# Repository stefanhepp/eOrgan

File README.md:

README
------

This project contains various parts of a midi-organ. The project consists of four
main parts:

- The Pedalboard: a 29 note midi foot pedal, mostly ARGO compliant. This odd number of notes
  was choosen because of size restrictions (I wanted it to fit under my e-piano).
- The organ console: contains stops, a lcd display, and all connectors and hardware to wire it to a PC.
  Up to three midi keyboards can be used as input devices, as well as the midi pedalboard.
- The organ desk: a framework for all the parts, contains speakers and some additional foot-stops.
  This is also designed to hold the PC. 
- The software: A controller software which allows access to some special features of the hardware
  and sets up the software synthesizer.

License
-------
Shield: [![CC BY-SA 4.0][cc-by-sa-shield]][cc-by-sa]

This work is licensed under a
[Creative Commons Attribution-ShareAlike 4.0 International License][cc-by-sa].

[![CC BY-SA 4.0][cc-by-sa-image]][cc-by-sa]

[cc-by-sa]: http://creativecommons.org/licenses/by-sa/4.0/
[cc-by-sa-image]: https://licensebuttons.net/l/by-sa/4.0/88x31.png
[cc-by-sa-shield]: https://img.shields.io/badge/License-CC%20BY--SA%204.0-lightgrey.svg

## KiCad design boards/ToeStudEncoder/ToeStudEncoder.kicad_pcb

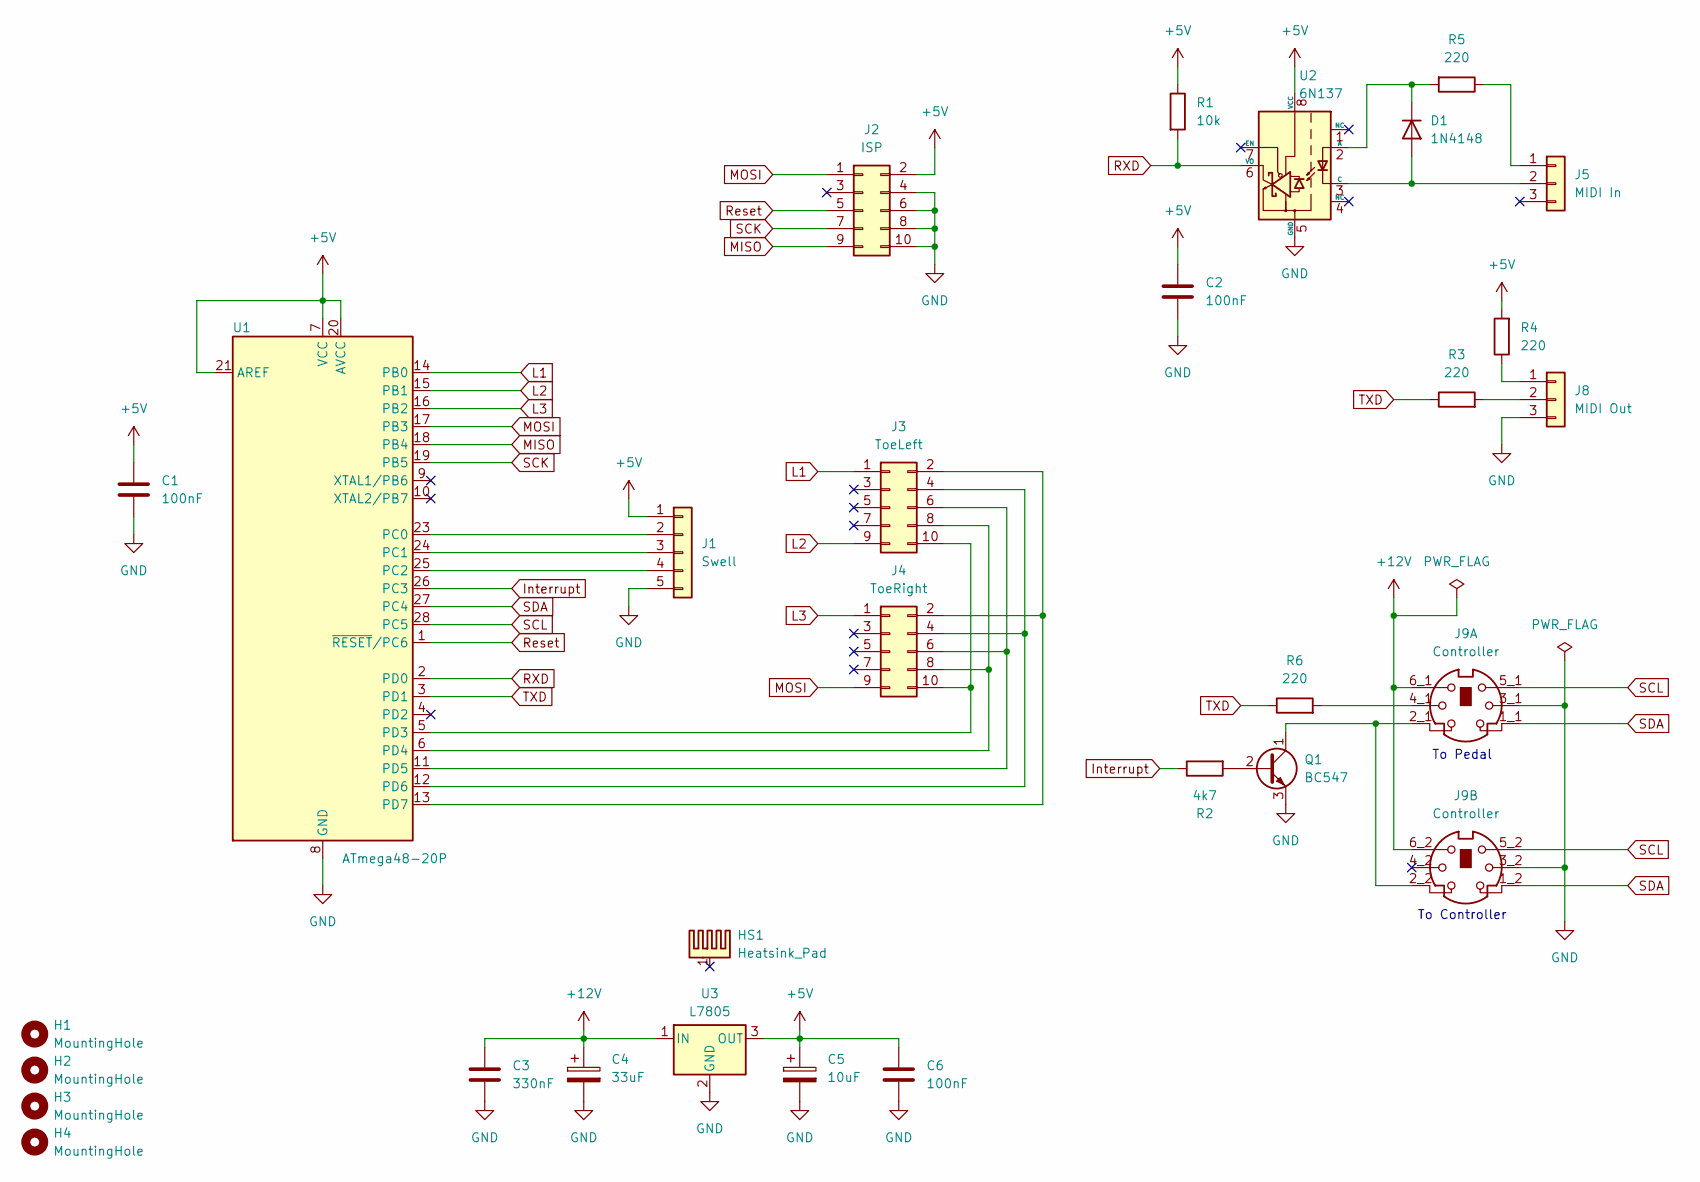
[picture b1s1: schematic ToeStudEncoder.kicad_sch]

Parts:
C1, C2: 100nF; C_Disc_D7.5mm_W2.5mm_P5.00mm
C3: 330nF; C_Disc_D4.3mm_W1.9mm_P5.00mm
C4: 33uF; CP_Radial_D7.5mm_P2.50mm
C5: 10uF; CP_Radial_D6.3mm_P2.50mm
C6: 100nF; C_Disc_D4.3mm_W1.9mm_P5.00mm
D1: 1N4148; D_DO-35_SOD27_P7.62mm_Horizontal
H1, H2, H3, H4: MountingHole; MountingHole_3mm
HS1: Heatsink_Pad; Heatsink_Aavid_TO-220_H12.7mm
J1: Swell; JST_XH_B5B-XH-A_1x05_P2.50mm_Vertical
J2: ISP; IDC-Header_2x05_P2.54mm_Vertical
J3: ToeLeft; IDC-Header_2x05_P2.54mm_Vertical
J4: ToeRight; IDC-Header_2x05_P2.54mm_Vertical
J5: MIDI In; PinHeader_1x03_P2.54mm_Vertical
J8: MIDI Out; PinHeader_1x03_P2.54mm_Vertical
J9: Controller; SWITCHCRAFT_DMD6FRA111
Q1: BC547; TO-92_Inline_Wide
R1: 10k; R_Axial_DIN0207_L6.3mm_D2.5mm_P2.54mm_Vertical
R2: 4k7; R_Axial_DIN0207_L6.3mm_D2.5mm_P2.54mm_Vertical
R3, R4, R6: 220; R_Axial_DIN0207_L6.3mm_D2.5mm_P10.16mm_Horizontal
R5: 220; R_Axial_DIN0207_L6.3mm_D2.5mm_P2.54mm_Vertical
U1: ATmega48-20P; DIP-28_W7.62mm
U2: 6N137; DIP-8_W7.62mm
U3: L7805; TO-220-3_Vertical

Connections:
+5V: C1.1, C2.1, C5.1, C6.1, J1.1, J2.2, R1.1, R4.2, U1.7 (VCC), U1.20 (AVCC), U1.21 (AREF), U2.8 (VCC), U3.3 (OUT)
+12V: C3.1, C4.1, J9.6_1, J9.6_2, U3.1 (IN)
GND: C1.2, C2.2, C3.2, C4.2, C5.2, C6.2, J1.5, J2.4, J2.6, J2.8, J2.10, J8.3, J9.3_1, J9.3_2, Q1.3 (E), U1.8 (GND), U1.22 (GND), U2.5 (GND), U3.2 (GND)
Interrupt: R2.1, U1.26 (PC3)
L1: J3.1, U1.14 (PB0)
L2: J3.9, U1.15 (PB1)
L3: J4.1, U1.16 (PB2)
MISO: J2.9, U1.18 (PB4)
MOSI: J2.1, J4.9, U1.17 (PB3)
unnamed: D1.2 (A), J5.2, U2.3 (C)
unnamed: D1.1 (K), R5.2, U2.2 (A)
unnamed: J1.2, U1.23 (PC0)
unnamed: J1.3, U1.24 (PC1)
unnamed: J1.4, U1.25 (PC2)
unnamed: J3.2, J4.2, U1.13 (PD7)
unnamed: J3.4, J4.4, U1.12 (PD6)
unnamed: J3.6, J4.6, U1.11 (PD5)
unnamed: J3.8, J4.8, U1.6 (PD4)
unnamed: J3.10, J4.10, U1.5 (PD3)
unnamed: J5.1, R5.1
unnamed: J8.1, R4.1
unnamed: J8.2, R3.2
unnamed: J9.4_1, R6.2
unnamed: Q1.2 (B), R2.2
unnamed: J9.2_1, J9.2_2, Q1.1 (C)
RXD: R1.2, U1.2 (PD0), U2.6 (VO)
Reset: J2.5, U1.1 (~RESET/PC6)
SCK: J2.7, U1.19 (PB5)
SCL: J9.5_1, J9.5_2, U1.28 (PC5)
SDA: J9.1_1, J9.1_2, U1.27 (PC4)
TXD: R3.1, R6.1, U1.3 (PD1)

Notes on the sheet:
To Controller
To Pedal

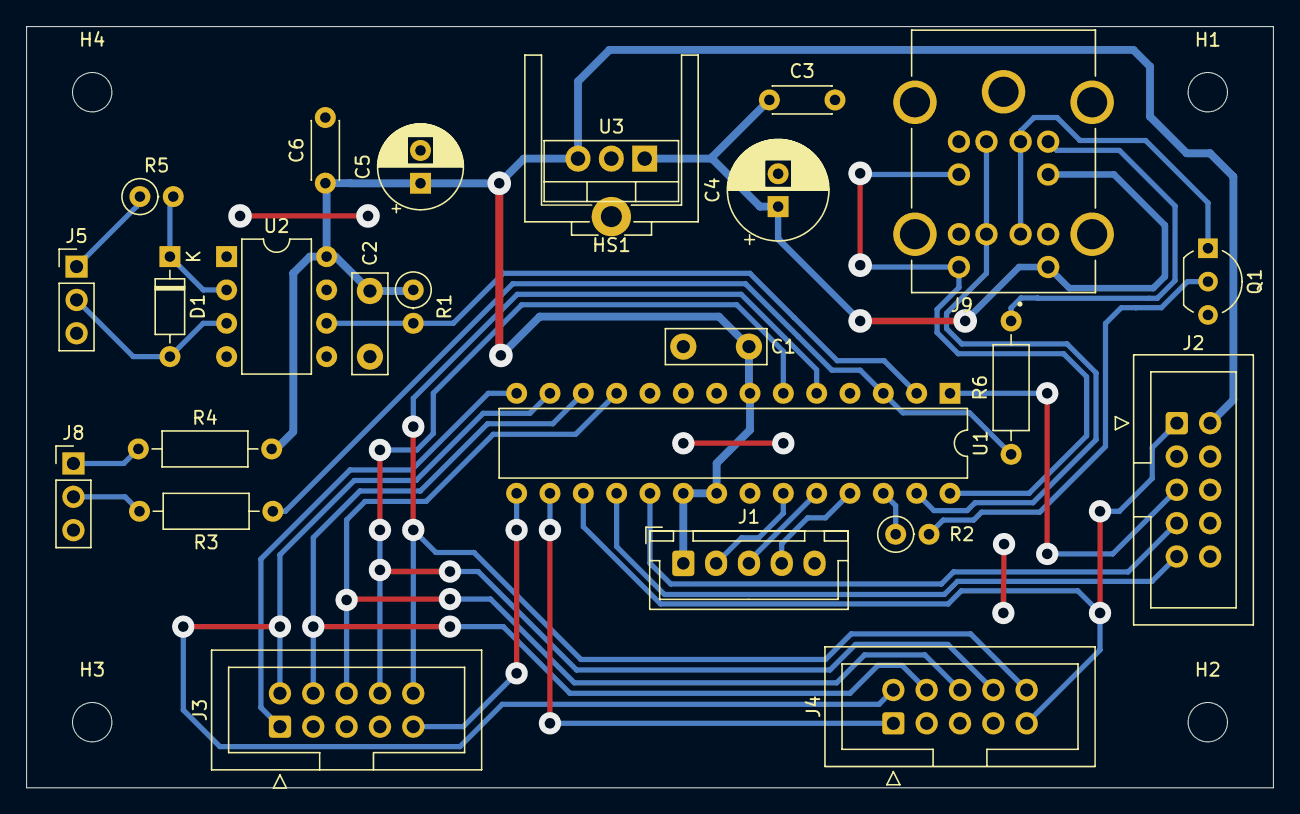
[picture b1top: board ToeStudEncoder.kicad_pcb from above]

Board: 2 copper layers, 95.0 x 58.0 mm, 29 parts (0 on the bottom side), 31 nets.

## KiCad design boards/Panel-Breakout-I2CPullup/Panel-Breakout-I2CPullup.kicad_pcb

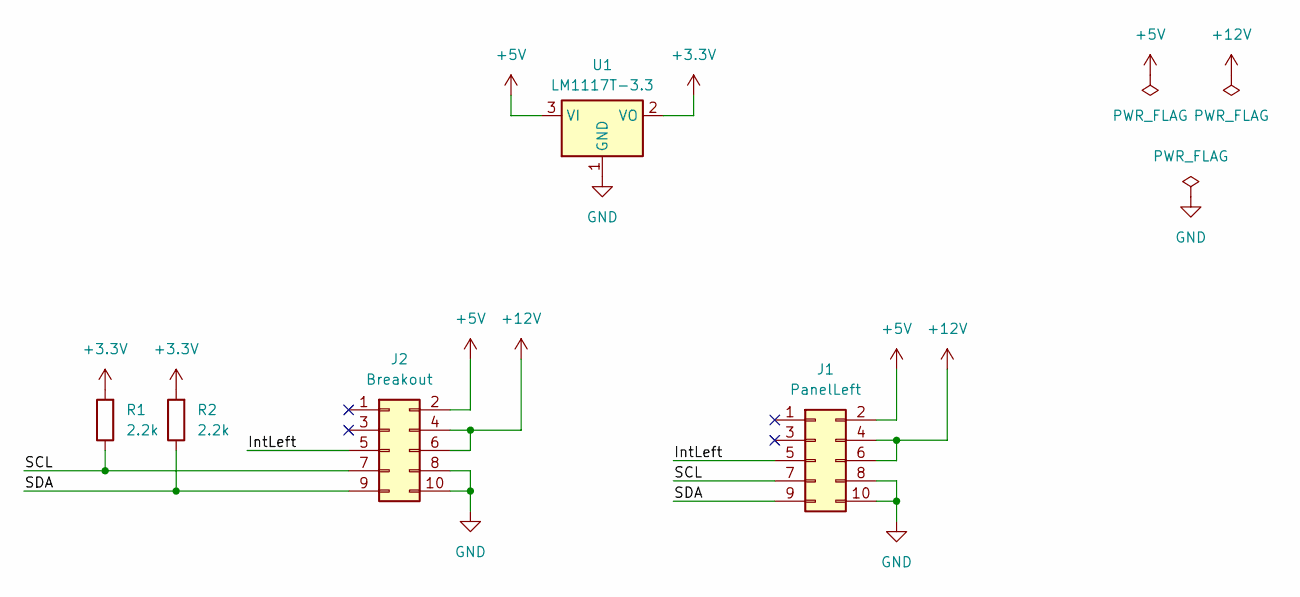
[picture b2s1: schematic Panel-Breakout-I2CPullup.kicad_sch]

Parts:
J1: PanelLeft; IDC-Header_2x05_P2.54mm_Vertical
J2: Breakout; IDC-Header_2x05_P2.54mm_Vertical
R1, R2: 2.2k; R_Axial_DIN0207_L6.3mm_D2.5mm_P10.16mm_Horizontal
U1: LM1117T-3.3; TO-220-3_Vertical

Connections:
+3.3V: R1.2, R2.2, U1.2 (VO)
+5V: J1.2, J2.2, U1.3 (VI)
+12V: J1.4, J1.6, J2.4, J2.6
/IntLeft: J1.5, J2.5
/SCL: J1.7, J2.7, R1.1
/SDA: J1.9, J2.9, R2.1
GND: J1.8, J1.10, J2.8, J2.10, U1.1 (GND)

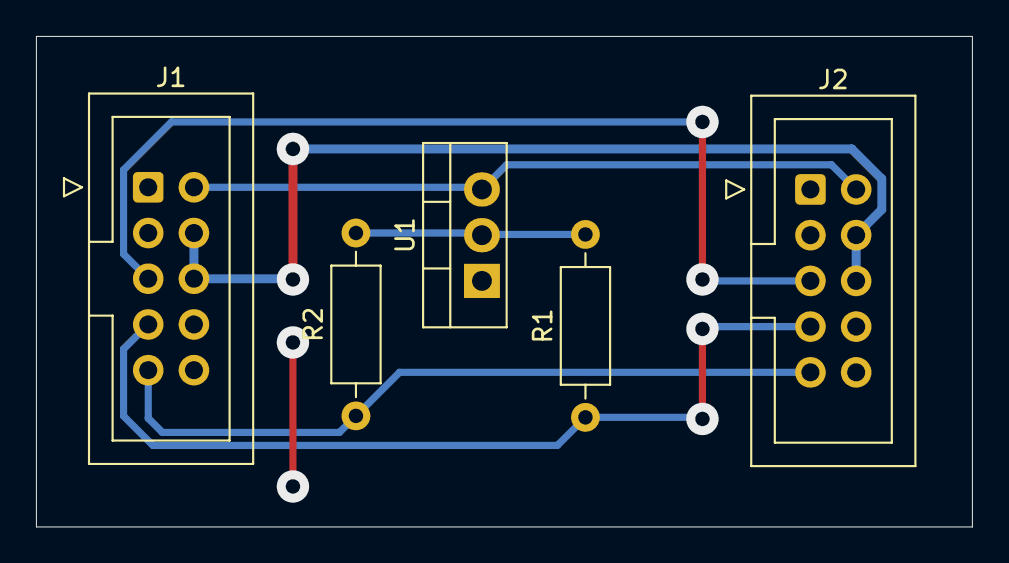
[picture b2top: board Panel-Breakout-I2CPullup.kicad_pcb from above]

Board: 2 copper layers, 52.0 x 27.2 mm, 5 parts (0 on the bottom side), 7 nets.

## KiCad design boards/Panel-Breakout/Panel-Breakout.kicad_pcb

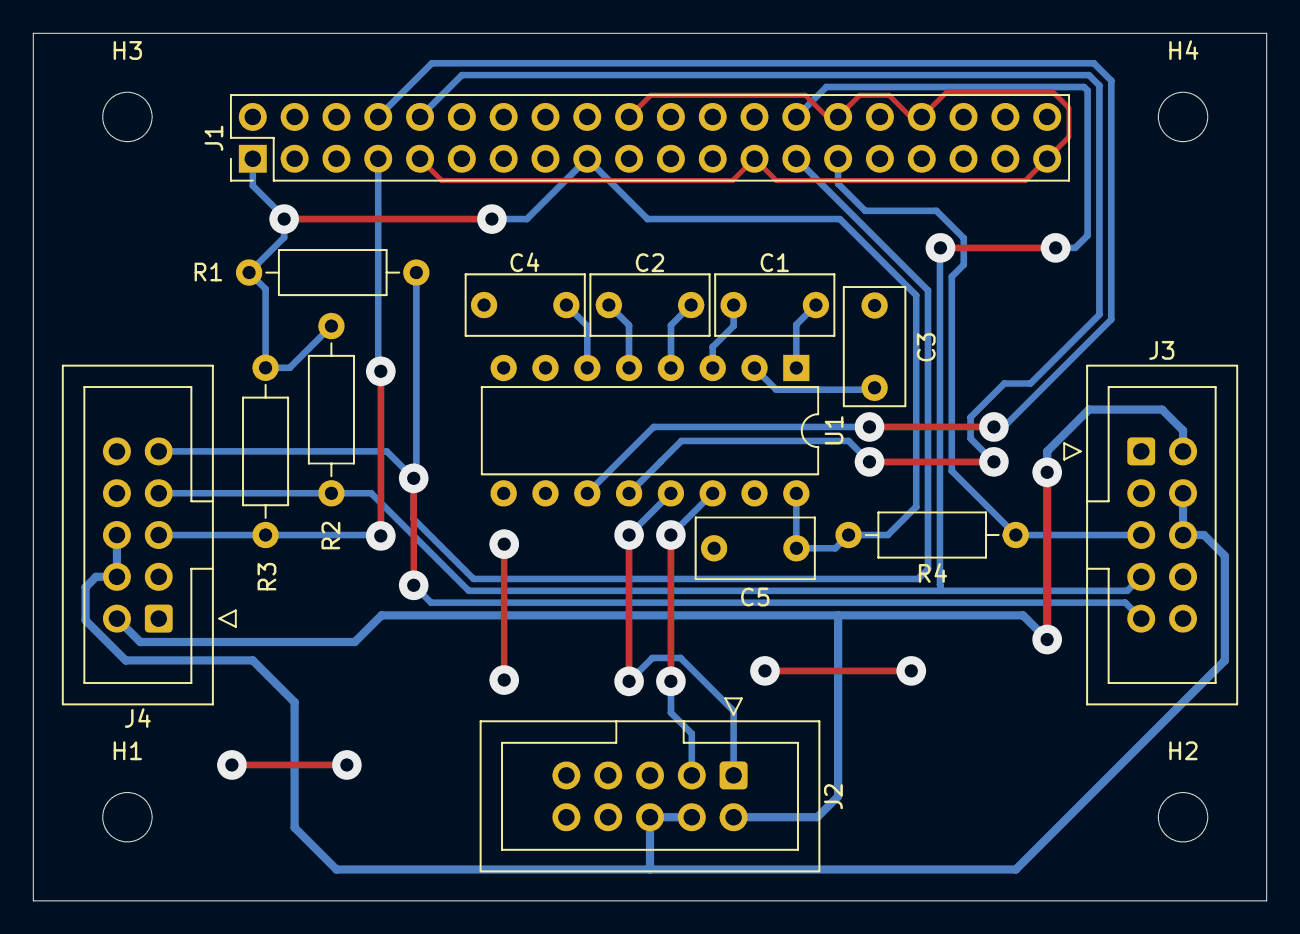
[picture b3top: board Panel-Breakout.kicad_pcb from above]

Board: 2 copper layers, 74.9 x 52.7 mm, 18 parts (0 on the bottom side), 18 nets.

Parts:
C1, C2, C3, C4, C5: 0.47uF; C_Rect_L7.0mm_W3.5mm_P5.00mm
H1, H2, H3, H4: MountingHole; MountingHole_3mm
J1: Raspberry_Pi_2_3; PinHeader_2x20_P2.54mm_Vertical
J2: BoardCon; IDC-Header_2x05_P2.54mm_Vertical
J3: PanelLeft; IDC-Header_2x05_P2.54mm_Vertical
J4: PanelRight; IDC-Header_2x05_P2.54mm_Vertical
R1, R2: 2.2k; R_Axial_DIN0207_L6.3mm_D2.5mm_P10.16mm_Horizontal
R3, R4: 10k; R_Axial_DIN0207_L6.3mm_D2.5mm_P10.16mm_Horizontal
U1: ICL3232; DIP-16_W7.62mm

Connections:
+3.3V: C5.1, J1.1 (3V3), J1.17 (3V3), R1.2, R2.2, R3.2, R4.2, U1.16 (VCC)
+5V: J2.2, J3.2, J4.2
+12V: J2.4, J2.6, J3.4, J3.6, J4.4, J4.6
/IntLeft: J1.29 (GCLK1/GPIO5), J3.5, R4.1
/IntRight: J1.7 (GCLK0/GPIO4), J4.5, R3.1
/RPI_RXD: J1.10 (GPIO15/RXD), U1.12 (R1OUT)
/RPI_TXD: J1.8 (GPIO14/TXD), U1.11 (T1IN)
/RS232_RXD: J2.1, U1.13 (R1IN)
/RS232_TXD: J2.3, U1.14 (T1OUT)
/SCL: J1.28 (ID_SC/GPIO1), J3.7, J4.7, R2.1
/SDA: J1.27 (ID_SD/GPIO0), J3.9, J4.9, R1.1
GND: C3.2, C4.2, C5.2, J1.6 (GND), J1.9 (GND), J1.14 (GND), J1.20 (GND), J1.25 (GND), J1.30 (GND), J1.34 (GND), J1.39 (GND), J2.8, J2.10, J3.8, J3.10, J4.8, J4.10, U1.8 (R2IN), U1.10 (T2IN), U1.15 (GND)
unnamed: C1.1, U1.1 (C1+)
unnamed: C1.2, U1.3 (C1-)
unnamed: C2.1, U1.4 (C2+)
unnamed: C2.2, U1.5 (C2-)
unnamed: C3.1, U1.2 (VS+)
unnamed: C4.1, U1.6 (VS-)

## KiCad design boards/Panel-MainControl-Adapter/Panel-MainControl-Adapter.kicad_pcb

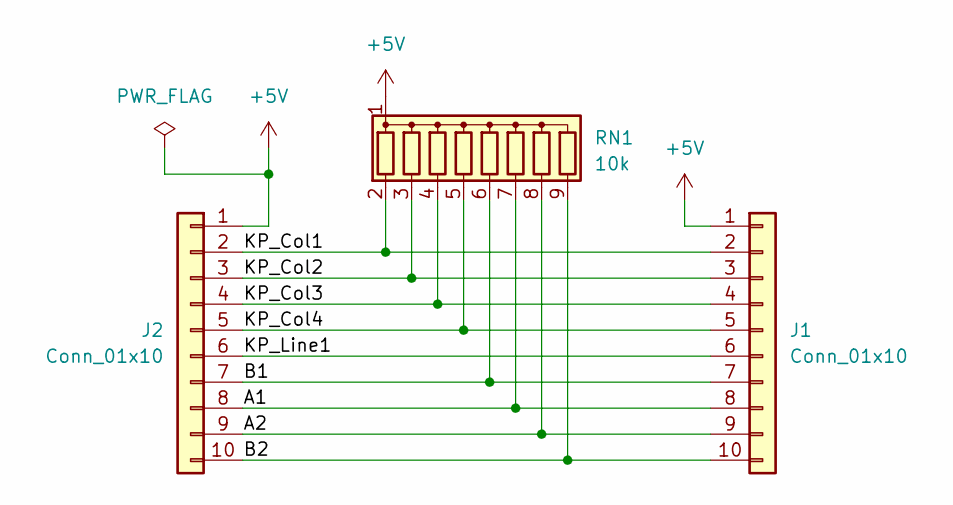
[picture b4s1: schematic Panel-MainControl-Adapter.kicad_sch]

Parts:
J1, J2: Conn_01x10; PinHeader_1x10_P2.00mm_Vertical
RN1: 10k; R_Array_SIP9

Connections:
+5V: J1.1, J2.1, RN1.1 (common)
/A1: J1.8, J2.8, RN1.7 (R6)
/A2: J1.9, J2.9, RN1.8 (R7)
/B1: J1.7, J2.7, RN1.6 (R5)
/B2: J1.10, J2.10, RN1.9 (R8)
/KP_Col1: J1.2, J2.2, RN1.2 (R1)
/KP_Col2: J1.3, J2.3, RN1.3 (R2)
/KP_Col3: J1.4, J2.4, RN1.4 (R3)
/KP_Col4: J1.5, J2.5, RN1.5 (R4)
/KP_Line1: J1.6, J2.6

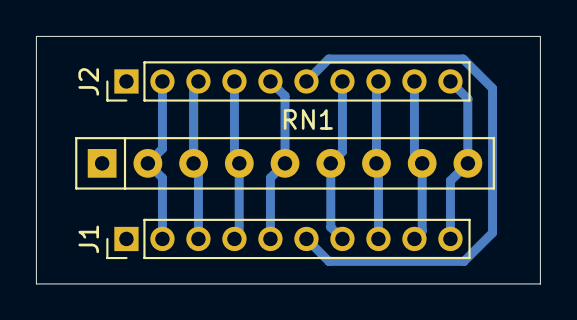
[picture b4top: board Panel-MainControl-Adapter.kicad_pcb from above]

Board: 2 copper layers, 28.0 x 13.8 mm, 3 parts (0 on the bottom side), 10 nets.

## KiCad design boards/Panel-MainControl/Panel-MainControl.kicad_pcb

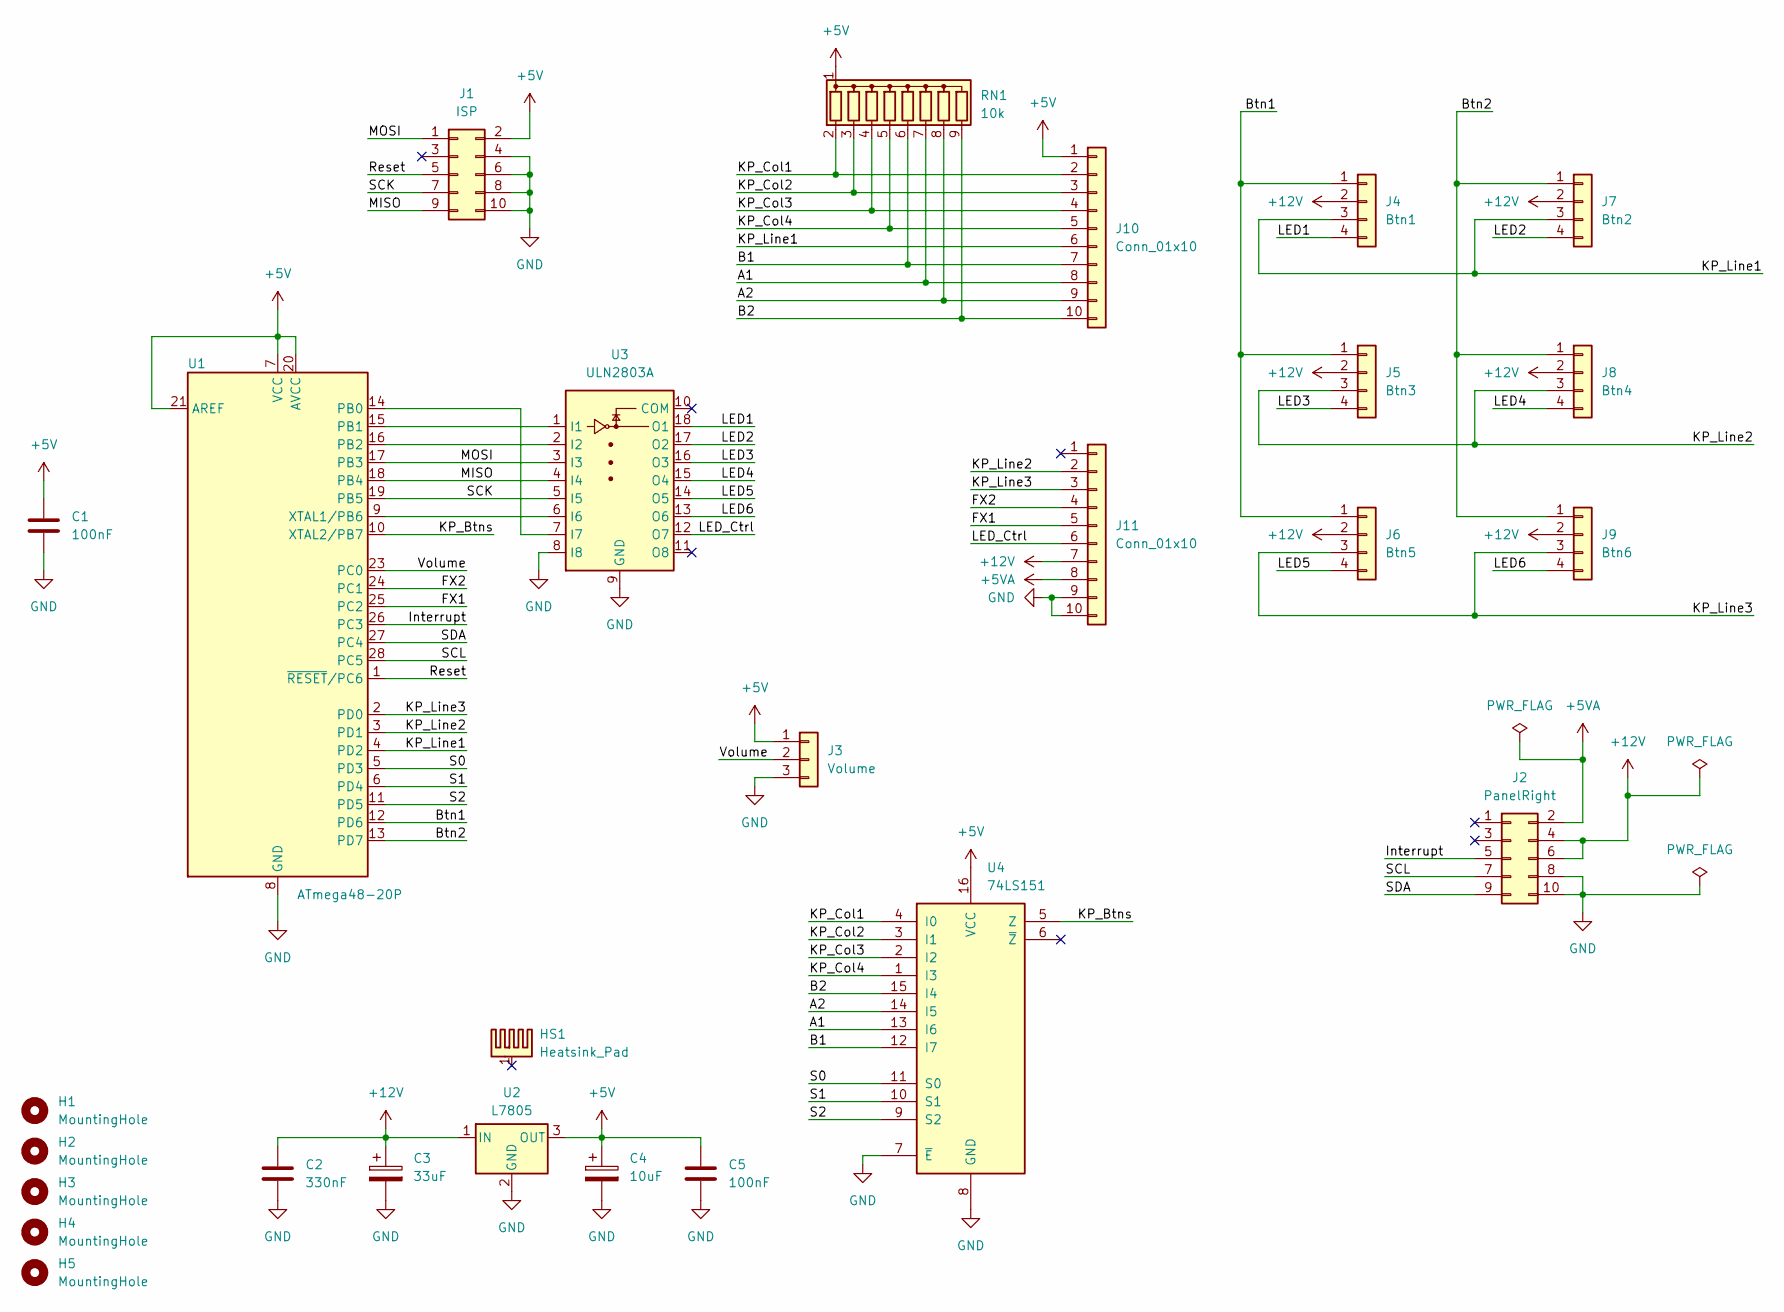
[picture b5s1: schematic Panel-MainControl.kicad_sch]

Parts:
C1, C5: 100nF; C_Disc_D4.3mm_W1.9mm_P5.00mm
C2: 330nF; C_Disc_D4.3mm_W1.9mm_P5.00mm
C3: 33uF; CP_Radial_D7.5mm_P2.50mm
C4: 10uF; CP_Radial_D6.3mm_P2.50mm
H1, H2, H3, H4, H5: MountingHole; MountingHole_2.7mm_M2.5
HS1: Heatsink_Pad; Heatsink_Aavid_TO-220_H12.7mm
J1: ISP; IDC-Header_2x05_P2.54mm_Vertical
J2: PanelRight; IDC-Header_2x05_P2.54mm_Vertical
J3: Volume; PinHeader_1x03_P2.54mm_Vertical
J4: Btn1; JST_XH_B4B-XH-A_1x04_P2.50mm_Vertical
J5: Btn3; JST_XH_B4B-XH-A_1x04_P2.50mm_Vertical
J6: Btn5; JST_XH_B4B-XH-A_1x04_P2.50mm_Vertical
J7: Btn2; JST_XH_B4B-XH-A_1x04_P2.50mm_Vertical
J8: Btn4; JST_XH_B4B-XH-A_1x04_P2.50mm_Vertical
J9: Btn6; JST_XH_B4B-XH-A_1x04_P2.50mm_Vertical
J10, J11: Conn_01x10; PinHeader_1x10_P2.00mm_Vertical
RN1: 10k; R_Array_SIP9
U1: ATmega48-20P; DIP-28_W7.62mm_Socket
U2: L7805; TO-220-3_Vertical
U3: ULN2803A; DIP-18_W7.62mm
U4: 74LS151; DIP-16_W7.62mm

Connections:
+5V: C1.1, C4.1, C5.1, J1.2, J3.1, J10.1, RN1.1 (common), U1.7 (VCC), U1.20 (AVCC), U1.21 (AREF), U2.3 (OUT), U4.16 (VCC)
+5VA: J2.2, J11.8
+12V: C2.1, C3.1, J2.4, J2.6, J4.2, J5.2, J6.2, J7.2, J8.2, J9.2, J11.7, U2.1 (IN)
/A1: J10.8, RN1.7 (R6), U4.13 (I6)
/A2: J10.9, RN1.8 (R7), U4.14 (I5)
/B1: J10.7, RN1.6 (R5), U4.12 (I7)
/B2: J10.10, RN1.9 (R8), U4.15 (I4)
/Btn1: J4.1, J5.1, J6.1, U1.12 (PD6)
/Btn2: J7.1, J8.1, J9.1, U1.13 (PD7)
/FX1: J11.5, U1.25 (PC2)
/FX2: J11.4, U1.24 (PC1)
/Interrupt: J2.5, U1.26 (PC3)
/KP_Btns: U1.10 (XTAL2/PB7), U4.5 (Z)
/KP_Col1: J10.2, RN1.2 (R1), U4.4 (I0)
/KP_Col2: J10.3, RN1.3 (R2), U4.3 (I1)
/KP_Col3: J10.4, RN1.4 (R3), U4.2 (I2)
/KP_Col4: J10.5, RN1.5 (R4), U4.1 (I3)
/KP_Line1: J4.3, J7.3, J10.6, U1.4 (PD2)
/KP_Line2: J5.3, J8.3, J11.2, U1.3 (PD1)
/KP_Line3: J6.3, J9.3, J11.3, U1.2 (PD0)
/LED1: J4.4, U3.18 (O1)
/LED2: J7.4, U3.17 (O2)
/LED3: J5.4, U3.16 (O3)
/LED4: J8.4, U3.15 (O4)
/LED5: J6.4, U3.14 (O5)
/LED6: J9.4, U3.13 (O6)
/LED_Ctrl: J11.6, U3.12 (O7)
/MISO: J1.9, U1.18 (PB4), U3.4 (I4)
/MOSI: J1.1, U1.17 (PB3), U3.3 (I3)
/Reset: J1.5, U1.1 (~RESET/PC6)
/S0: U1.5 (PD3), U4.11 (S0)
/S1: U1.6 (PD4), U4.10 (S1)
/S2: U1.11 (PD5), U4.9 (S2)
/SCK: J1.7, U1.19 (PB5), U3.5 (I5)
/SCL: J2.7, U1.28 (PC5)
/SDA: J2.9, U1.27 (PC4)
/Volume: J3.2, U1.23 (PC0)
GND: C1.2, C2.2, C3.2, C4.2, C5.2, J1.4, J1.6, J1.8, J1.10, J2.8, J2.10, J3.3, J11.9, J11.10, U1.8 (GND), U1.22 (GND), U2.2 (GND), U3.8 (I8), U3.9 (GND), U4.7 (~E), U4.8 (GND)
unnamed: U1.14 (PB0), U3.7 (I7)
unnamed: U1.15 (PB1), U3.1 (I1)
unnamed: U1.16 (PB2), U3.2 (I2)
unnamed: U1.9 (XTAL1/PB6), U3.6 (I6)

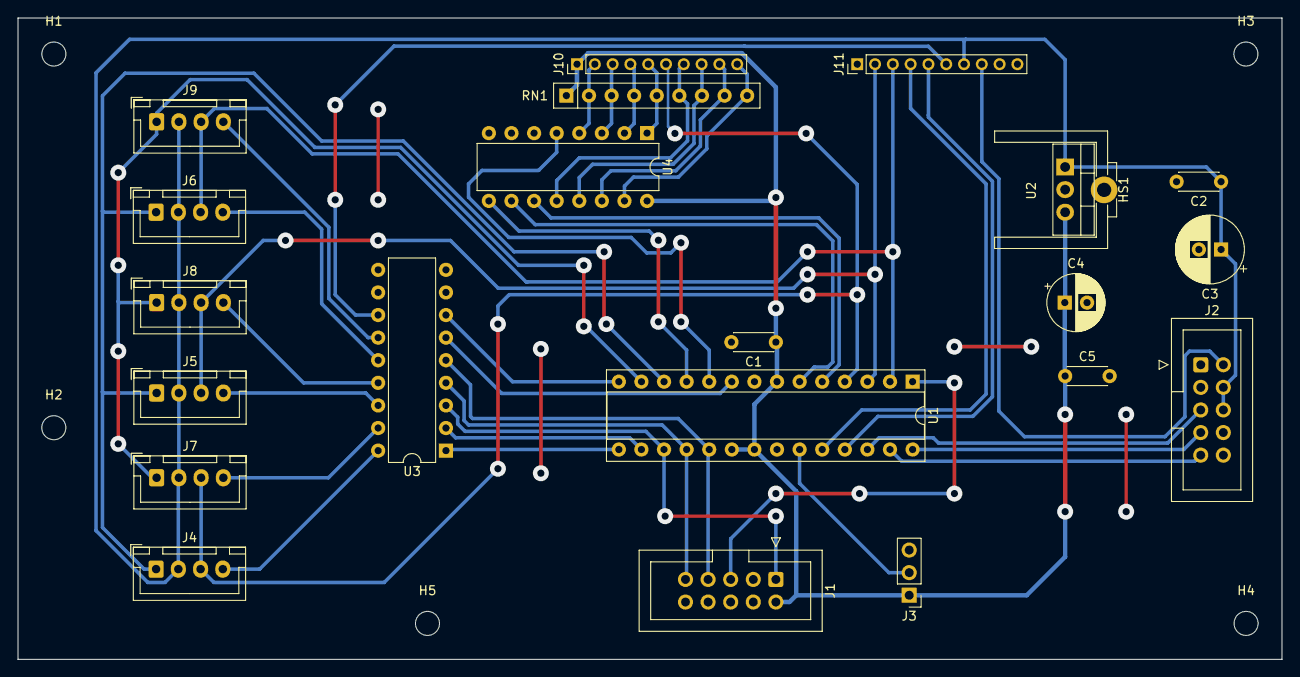
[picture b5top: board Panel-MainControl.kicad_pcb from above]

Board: 2 copper layers, 142.1 x 72.1 mm, 27 parts (0 on the bottom side), 42 nets.

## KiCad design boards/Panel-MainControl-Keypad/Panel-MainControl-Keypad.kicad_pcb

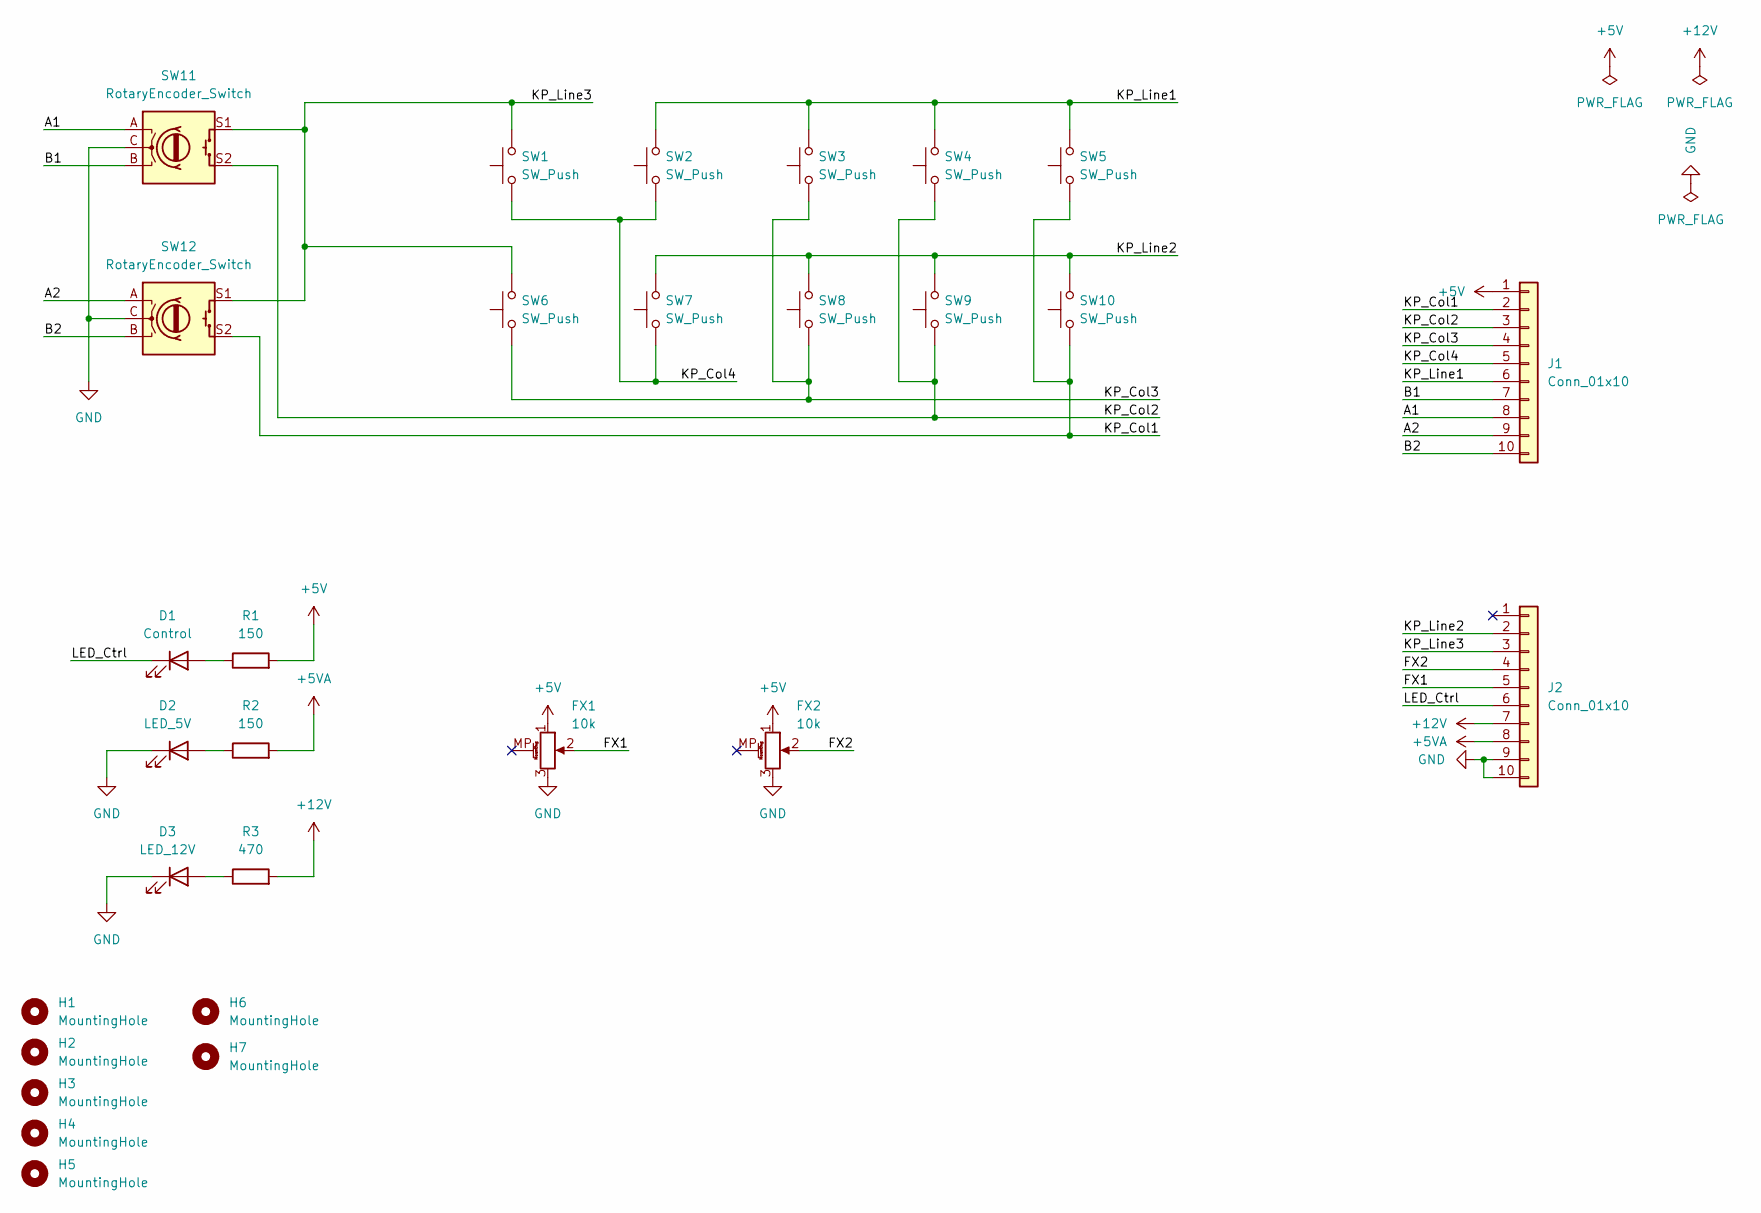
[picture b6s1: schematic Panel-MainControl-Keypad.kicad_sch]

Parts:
D1: Control; LED_Rectangular_W5.0mm_H2.0mm
D2: LED_5V; LED_Rectangular_W5.0mm_H2.0mm
D3: LED_12V; LED_Rectangular_W5.0mm_H2.0mm
FX1, FX2: 10k; Potentiometer_Alps_RK09K_Single_Vertical
H1, H2, H3, H4, H5, H6, H7: MountingHole; MountingHole_2.7mm_M2.5
J1, J2: Conn_01x10; PinHeader_1x10_P2.00mm_Vertical
R1, R2: 150; R_Axial_DIN0207_L6.3mm_D2.5mm_P10.16mm_Horizontal
R3: 470; R_Axial_DIN0207_L6.3mm_D2.5mm_P10.16mm_Horizontal
SW1, SW2, SW3, SW4, SW5, SW6, SW7, SW8, SW9, SW10: SW_Push; SW_PUSH_6mm_H9.5mm
SW11, SW12: RotaryEncoder_Switch; RotaryEncoder_Switch-PEC11R-4215F

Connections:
+5V: FX1.1, FX2.1, J1.1, R1.2
+5VA: J2.8, R2.2
+12V: J2.7, R3.2
/A1: J1.8, SW11.A
/A2: J1.9, SW12.A
/B1: J1.7, SW11.B
/B2: J1.10, SW12.B
/FX1: FX1.2, J2.5
/FX2: FX2.2, J2.4
/KP_Col1: J1.2, SW5.1, SW10.1, SW12.S2
/KP_Col2: J1.3, SW4.1, SW9.1, SW11.S2
/KP_Col3: J1.4, SW3.1, SW6.1, SW8.1
/KP_Col4: J1.5, SW1.1, SW2.1, SW7.1
/KP_Line1: J1.6, SW2.2, SW3.2, SW4.2, SW5.2
/KP_Line2: J2.2, SW7.2, SW8.2, SW9.2, SW10.2
/KP_Line3: J2.3, SW1.2, SW6.2, SW11.S1, SW12.S1
/LED_Ctrl: D1.1 (K), J2.6
GND: D2.1 (K), D3.1 (K), FX1.3, FX2.3, J2.9, J2.10, SW11.C, SW12.C
unnamed: D1.2 (A), R1.1
unnamed: D2.2 (A), R2.1
unnamed: D3.2 (A), R3.1

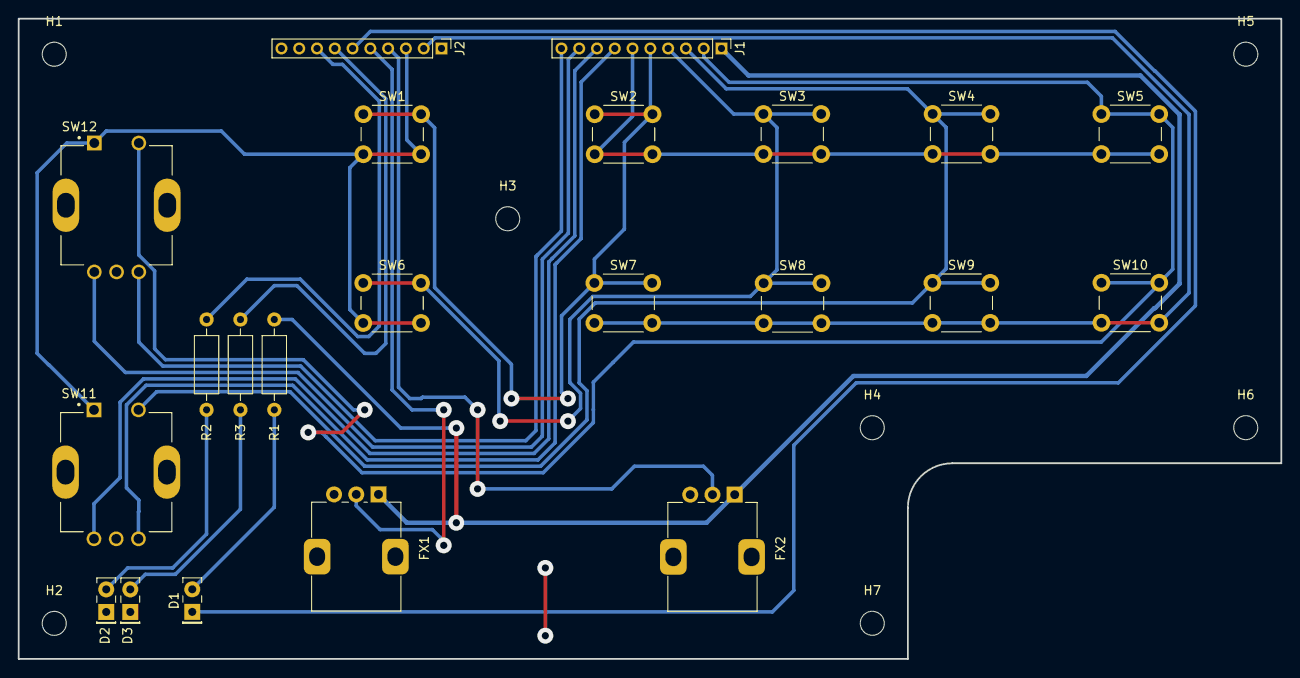
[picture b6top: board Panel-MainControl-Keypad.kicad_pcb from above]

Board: 2 copper layers, 142.0 x 72.0 mm, 29 parts (0 on the bottom side), 21 nets.

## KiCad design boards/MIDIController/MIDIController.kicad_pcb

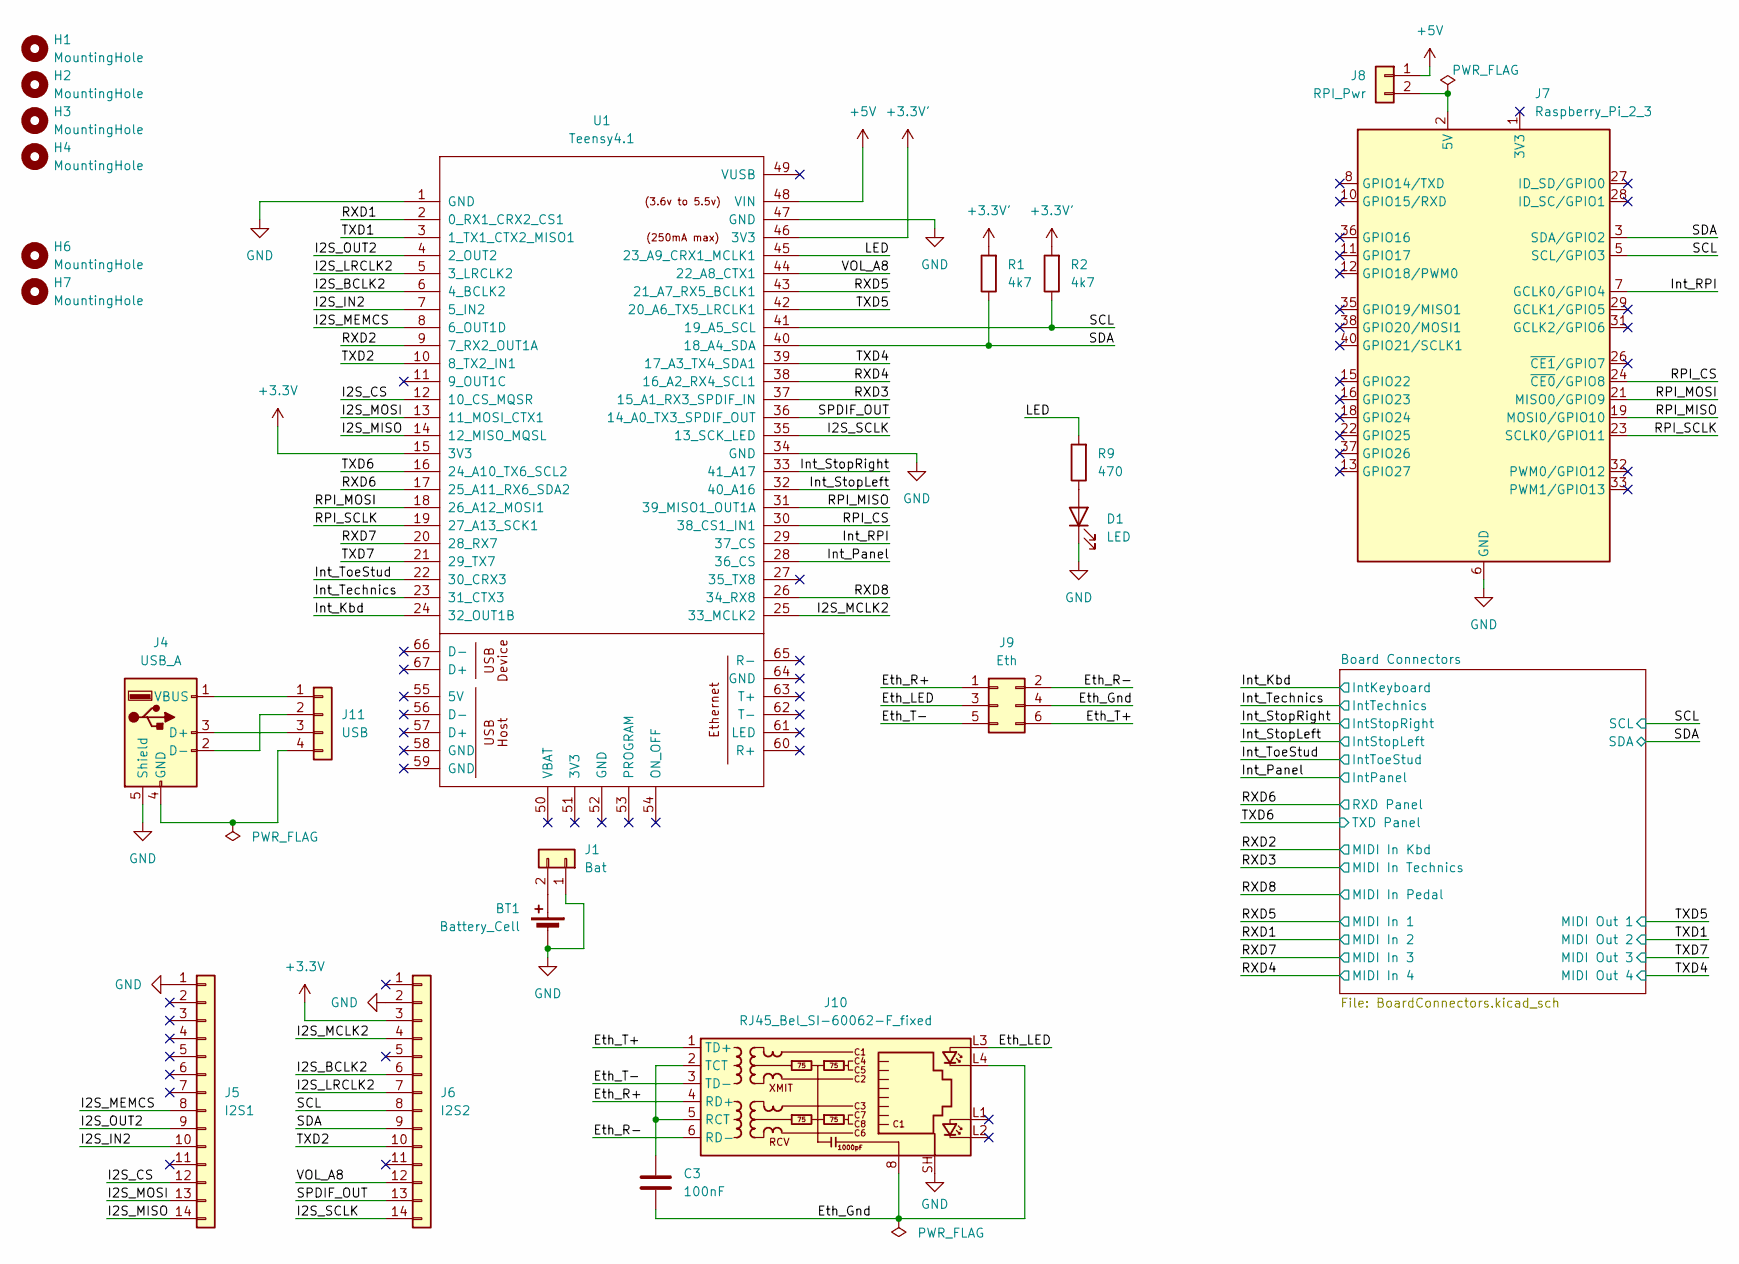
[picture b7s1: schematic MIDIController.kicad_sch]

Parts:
BT1: Battery_Cell; BatteryHolder_Holder_CR2032
C3: 100nF; C_Disc_D4.3mm_W1.9mm_P5.00mm
D1: LED; LED_D3.0mm
H1, H2, H3, H4: MountingHole; MountingHole_3.2mm_M3
H6, H7: MountingHole; MountingHole_2.7mm_M2.5
J1: Bat; PinHeader_1x02_P2.54mm_Vertical
J4: USB_A; USB_A_Molex_67643_Horizontal
J5: I2S1; PinHeader_1x14_P2.54mm_Vertical
J6: I2S2; PinHeader_1x14_P2.54mm_Vertical
J7: Raspberry_Pi_2_3; PinHeader_2x20_P2.54mm_Vertical
J8: RPI_Pwr; PinHeader_1x02_P2.54mm_Vertical
J9: Eth; PinHeader_2x03_P2.00mm_Vertical
J10: RJ45_Bel_SI-60062-F_fixed; RJ45_Bel_SI-60062-F
J11: USB; PinHeader_1x04_P2.54mm_Vertical
R1, R2: 4k7; R_Axial_DIN0207_L6.3mm_D2.5mm_P10.16mm_Horizontal
R9: 470; R_Axial_DIN0207_L6.3mm_D2.5mm_P10.16mm_Horizontal
U1: Teensy4.1; Teensy41

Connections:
+3.3V: J6.3, U1.15 (3V3); also elsewhere on the board
+3.3V': R1.2, R2.2, U1.46 (3V3)
+5V: J8.1, U1.48 (VIN); also elsewhere on the board
/Eth_Gnd: C3.2, J9.4, J10.8, J10.L4
/Eth_LED: J9.3, J10.L3
/Eth_R+: J9.1, J10.4 (RD+)
/Eth_R-: J9.2, J10.6 (RD-)
/Eth_T+: J9.6, J10.1 (TD+)
/Eth_T-: J9.5, J10.3 (TD-)
/I2S_BCLK2: J6.6, U1.6 (4_BCLK2)
/I2S_CS: J5.12, U1.12 (10_CS_MQSR)
/I2S_IN2: J5.10, U1.7 (5_IN2)
/I2S_LRCLK2: J6.7, U1.5 (3_LRCLK2)
/I2S_MCLK2: J6.4, U1.25 (33_MCLK2)
/I2S_MEMCS: J5.8, U1.8 (6_OUT1D)
/I2S_MISO: J5.14, U1.14 (12_MISO_MQSL)
/I2S_MOSI: J5.13, U1.13 (11_MOSI_CTX1)
/I2S_OUT2: J5.9, U1.4 (2_OUT2)
/I2S_SCLK: J6.14, U1.35 (13_SCK_LED)
/Int_Kbd: U1.24 (32_OUT1B); also elsewhere on the board
/Int_Panel: U1.28 (36_CS); also elsewhere on the board
/Int_RPI: J7.7 (GCLK0/GPIO4), U1.29 (37_CS)
/Int_StopLeft: U1.32 (40_A16); also elsewhere on the board
/Int_StopRight: U1.33 (41_A17); also elsewhere on the board
/Int_Technics: U1.23 (31_CTX3); also elsewhere on the board
/Int_ToeStud: U1.22 (30_CRX3); also elsewhere on the board
/LED: R9.2, U1.45 (23_A9_CRX1_MCLK1)
/RPI_CS: J7.24 (~CE0/GPIO8), U1.30 (38_CS1_IN1)
/RPI_MISO: J7.19 (MOSI0/GPIO10), U1.31 (39_MISO1_OUT1A)
/RPI_MOSI: J7.21 (MISO0/GPIO9), U1.18 (26_A12_MOSI1)
/RPI_SCLK: J7.23 (SCLK0/GPIO11), U1.19 (27_A13_SCK1)
/RXD1: U1.2 (0_RX1_CRX2_CS1); also elsewhere on the board
/RXD2: U1.9 (7_RX2_OUT1A); also elsewhere on the board
/RXD3: U1.37 (15_A1_RX3_SPDIF_IN); also elsewhere on the board
/RXD4: U1.38 (16_A2_RX4_SCL1); also elsewhere on the board
/RXD5: U1.43 (21_A7_RX5_BCLK1); also elsewhere on the board
/RXD6: U1.17 (25_A11_RX6_SDA2); also elsewhere on the board
/RXD7: U1.20 (28_RX7); also elsewhere on the board
/RXD8: U1.26 (34_RX8); also elsewhere on the board
/SCL: J6.8, J7.5 (SCL/GPIO3), R2.1, U1.41 (19_A5_SCL); also elsewhere on the board
/SDA: J6.9, J7.3 (SDA/GPIO2), R1.1, U1.40 (18_A4_SDA); also elsewhere on the board
/SPDIF_OUT: J6.13, U1.36 (14_A0_TX3_SPDIF_OUT)
/TXD1: U1.3 (1_TX1_CTX2_MISO1); also elsewhere on the board
/TXD2: J6.10, U1.10 (8_TX2_IN1)
/TXD4: U1.39 (17_A3_TX4_SDA1); also elsewhere on the board
/TXD5: U1.42 (20_A6_TX5_LRCLK1); also elsewhere on the board
/TXD6: U1.16 (24_A10_TX6_SCL2); also elsewhere on the board
/TXD7: U1.21 (29_TX7); also elsewhere on the board
/VOL_A8: J6.12, U1.44 (22_A8_CTX1)
GND: BT1.2 (-), D1.1 (K), J1.1, J4.5 (Shield), J5.1, J6.2, J7.6 (GND), J7.9 (GND), J7.14 (GND), J7.20 (GND), J7.25 (GND), J7.30 (GND), J7.34 (GND), J7.39 (GND), J10.SH, U1.1 (GND), U1.34 (GND), U1.47 (GND); also elsewhere on the board
unnamed: BT1.1 (+), J1.2
unnamed: D1.2 (A), R9.1
unnamed: J7.2 (5V), J7.4 (5V), J8.2
unnamed: C3.1, J10.2 (TCT), J10.5 (RCT)
unnamed: J4.1 (VBUS), J11.1
unnamed: J4.2 (D-), J11.2
unnamed: J4.3 (D+), J11.3
unnamed: J4.4 (GND), J11.4
